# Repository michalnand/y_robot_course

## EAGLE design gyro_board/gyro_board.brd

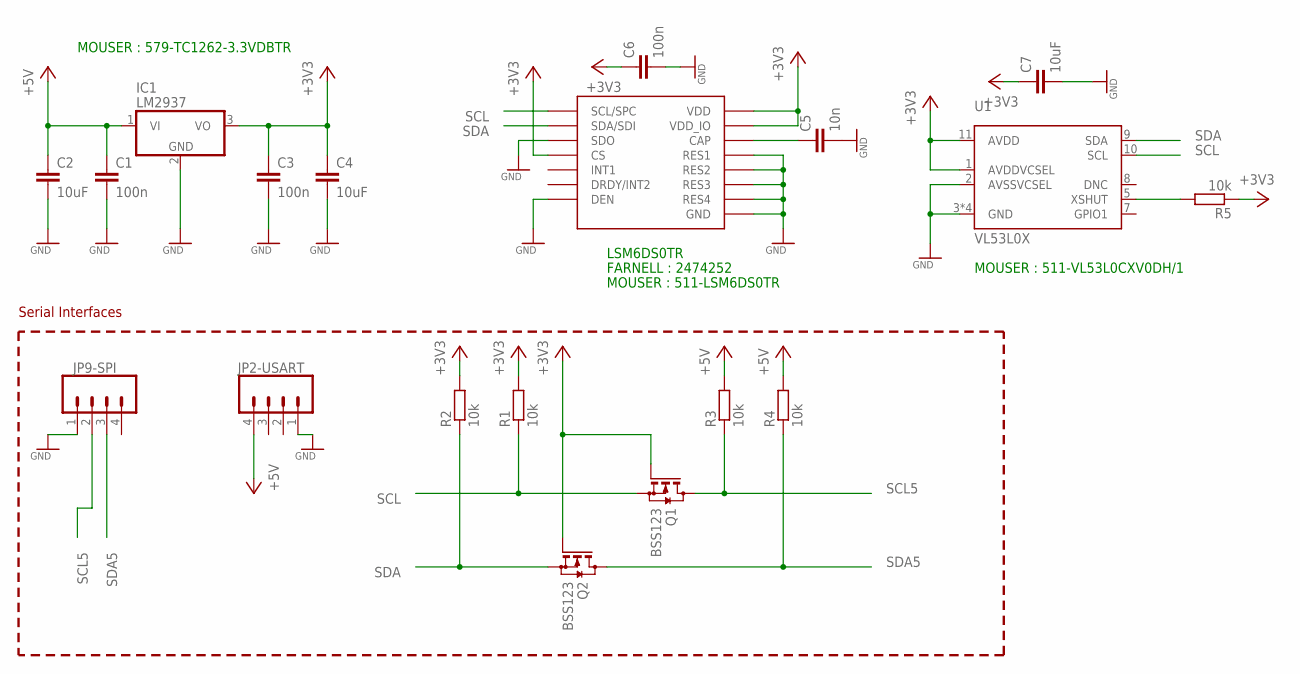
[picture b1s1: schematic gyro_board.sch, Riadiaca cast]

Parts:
C1, C3, C6: 100n; C0805K
C2, C4, C7: 10uF; C0805K
C5: 10n; C0805K
IC1: LM2937; TO263-3
JP2-USART, JP9-SPI: M04PTH; 1X04
LSM6DS0TR: L3GD20H; LGA16L
Q1, Q2: BSS123; SOT23
R1, R2, R3, R4, R5: 10k; R0805
U1: VL53L0X

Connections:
+3V3: C3.1, C4.1, C6.1, C7.1, IC1.3 (VO), LSM6DS0TR.P$1 (VDD_IO), LSM6DS0TR.P$5 (CS), LSM6DS0TR.P$16 (VDD), Q1.1 (G), Q2.1 (G), R1.2, R2.2, R5.1, U1.1 (AVDDVCSEL), U1.11 (AVDD)
+5V: C1.1, C2.1, IC1.1 (VI), JP2-USART.4, R3.2, R4.2
GND: C1.2, C2.2, C3.2, C4.2, C5.2, C6.2, C7.2, IC1.2 (GND), JP2-USART.1, JP9-SPI.1, LSM6DS0TR.P$4 (SDO), LSM6DS0TR.P$8 (DEN), LSM6DS0TR.P$9 (RES1), LSM6DS0TR.P$10 (RES2), LSM6DS0TR.P$11 (RES3), LSM6DS0TR.P$12 (GND), LSM6DS0TR.P$13 (GND), LSM6DS0TR.P$15 (RES4), U1.2 (AVSSVCSEL), U1.3 (GND), U1.4 (GND), U1.6 (GND), U1.12 (GND)
unnamed: C5.1, LSM6DS0TR.P$14 (CAP)
unnamed: R5.2, U1.5 (XSHUT)
SCL: LSM6DS0TR.P$2 (SCL/SPC), Q1.2 (S), R1.1, U1.10 (SCL)
SCL5: JP9-SPI.2, Q1.3 (D), R3.1
SDA: LSM6DS0TR.P$3 (SDA/SDI), Q2.2 (S), R2.1, U1.9 (SDA)
SDA5: JP9-SPI.3, Q2.3 (D), R4.1

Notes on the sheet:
Serial Interfaces
LSM6DS0TR
FARNELL : 2474252
MOUSER : 511-LSM6DS0TR
MOUSER : 511-VL53L0CXV0DH/1
MOUSER : 579-TC1262-3.3VDBTR

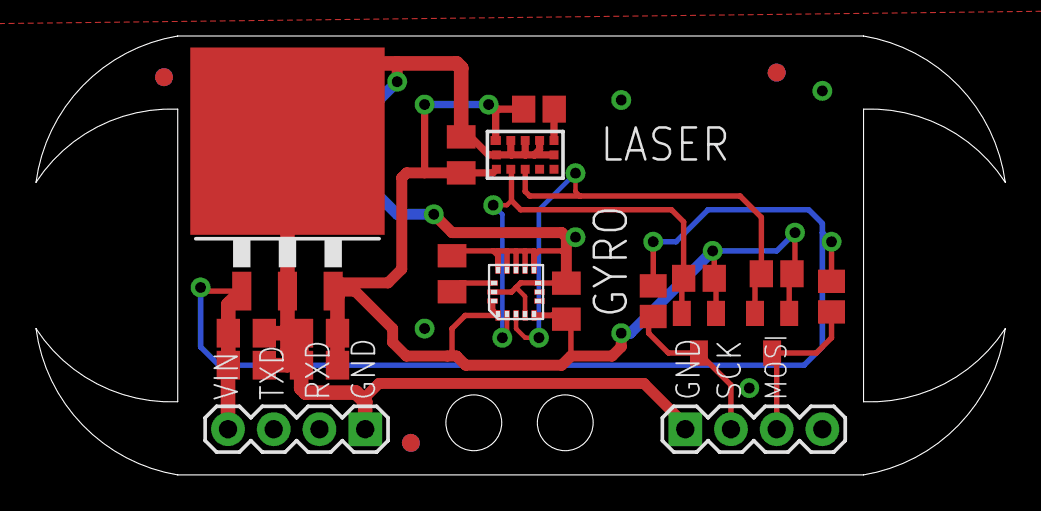
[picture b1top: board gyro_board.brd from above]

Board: 2 copper layers, 53.8 x 24.4 mm, 22 parts (0 on the bottom side), 9 nets.

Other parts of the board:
U$1, U$2, U$3: CIRCLE-1MM-2R

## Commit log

2017-06-20 common
2017-06-27 gyro lib - still no working
2017-06-29 gyro is working
2017-07-11 gyroscope example
2017-07-12 functor like os added
2017-08-31 presentation
2018-01-16 board
2018-02-09 tests
2018-06-08 camera
